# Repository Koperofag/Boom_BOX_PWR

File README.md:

# Boom_BOX_PWR
Circuit for powering audio amplifier using a 3S llithium battery and charging circuit for it.

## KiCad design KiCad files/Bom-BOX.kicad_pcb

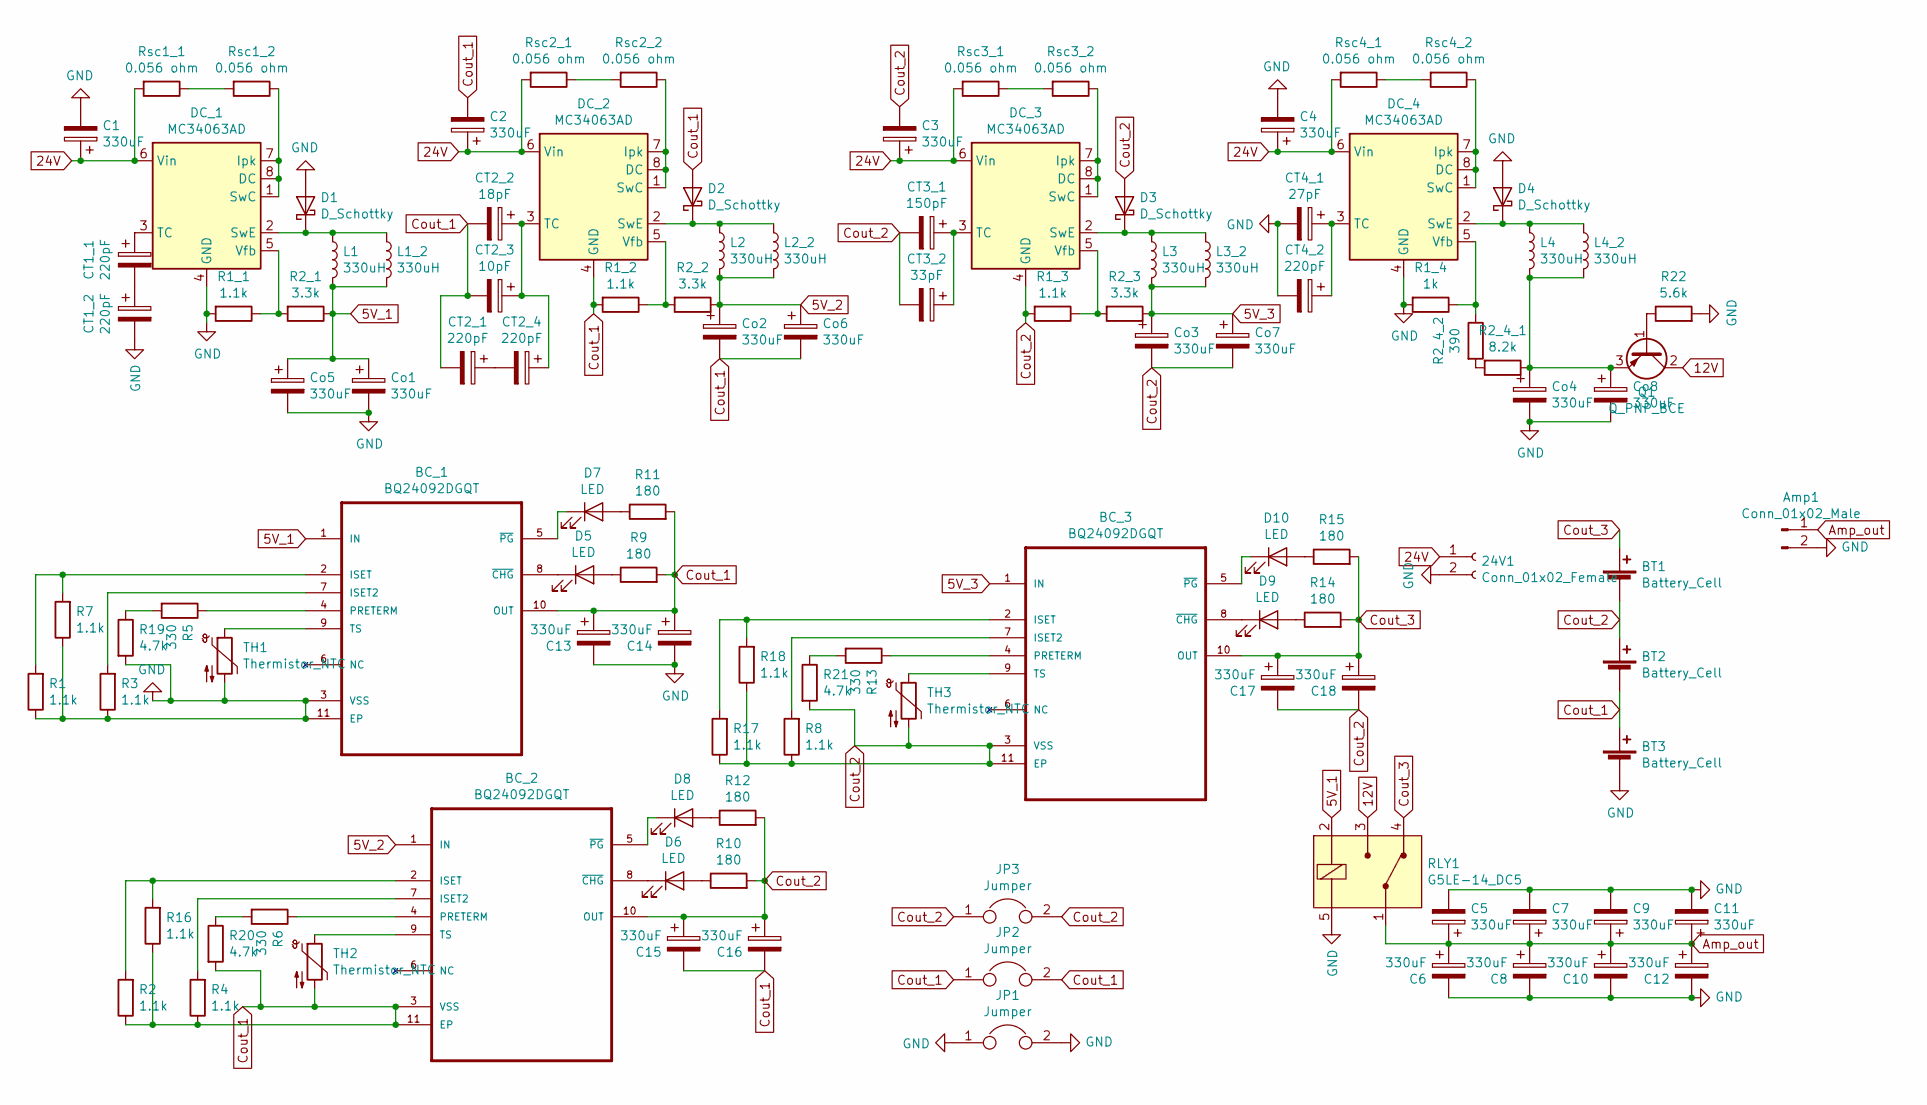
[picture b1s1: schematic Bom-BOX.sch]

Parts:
24V1: Conn_01x02_Female; TerminalBlock_RND_205-00001_1x02_P5.00mm_Horizontal
Amp1: Conn_01x02_Male; TerminalBlock_RND_205-00001_1x02_P5.00mm_Horizontal
BC_1, BC_2, BC_3: BQ24092DGQT; SOP50P490X110-11N
BT1, BT2, BT3: Battery_Cell; TerminalBlock_RND_205-00001_1x02_P5.00mm_Horizontal
C1, C2, C3, C4, C5, C6, C7, C8, C9, C10, C11, C12, C13, C14, C15, C16, C17, C18: 330uF; CP_Radial_D8.0mm_P5.00mm
CT1_1, CT1_2, CT2_1, CT2_4, CT4_2: 220pF; C_0603_1608Metric_Pad1.05x0.95mm_HandSolder
CT2_2: 18pF; C_0603_1608Metric_Pad1.05x0.95mm_HandSolder
CT2_3: 10pF; C_0603_1608Metric_Pad1.05x0.95mm_HandSolder
CT3_1: 150pF; C_0603_1608Metric_Pad1.05x0.95mm_HandSolder
CT3_2: 33pF; C_0603_1608Metric_Pad1.05x0.95mm_HandSolder
CT4_1: 27pF; C_0603_1608Metric_Pad1.05x0.95mm_HandSolder
Co1, Co2, Co3, Co4, Co5, Co6, Co7, Co8: 330uF; CP_Radial_D8.0mm_P5.00mm
D1, D2, D3, D4: D_Schottky; DO-214AB_ALT
D5, D6, D7, D8, D9, D10: LED; LED_D5.0mm
DC_1, DC_2, DC_3, DC_4: MC34063AD; SOIC-8_3.9x4.9mm_P1.27mm
JP1, JP2, JP3: Jumper; SolderWirePad_1x02_P3.81mm_Drill1mm
L1, L1_2, L2, L2_2, L3, L3_2, L4, L4_2: 330uH; L_Bourns_SRR1210A
Q1: Q_PNP_BCE; TO-220-3_Vertical
R1, R1_1, R1_2, R1_3, R2, R3, R4, R7, R8, R16, R17, R18: 1.1k; R_0603_1608Metric_Pad1.05x0.95mm_HandSolder
R1_4: 1k; R_0805_2012Metric_Pad1.15x1.40mm_HandSolder
R2_1, R2_2, R2_3: 3.3k; R_0805_2012Metric_Pad1.15x1.40mm_HandSolder
R2_4_1: 8.2k; R_0805_2012Metric_Pad1.15x1.40mm_HandSolder
R2_4_2: 390; R_0805_2012Metric_Pad1.15x1.40mm_HandSolder
R5, R6, R13: 330; R_0805_2012Metric_Pad1.15x1.40mm_HandSolder
R9, R10, R11, R12, R14, R15: 180; R_0603_1608Metric_Pad1.05x0.95mm_HandSolder
R19, R20, R21: 4.7k; R_0805_2012Metric_Pad1.15x1.40mm_HandSolder
R22: 5.6k; R_Axial_DIN0207_L6.3mm_D2.5mm_P10.16mm_Horizontal
RLY1: G5LE-14_DC5; Relay_THT_G5LE-14; MPN G5LE-14 DC5; Digi-Key_PN Z1011-ND
Rsc1_1, Rsc1_2, Rsc2_1, Rsc2_2, Rsc3_1, Rsc3_2, Rsc4_1, Rsc4_2: 0.056 ohm; C_0805_2012Metric_Pad1.15x1.40mm_HandSolder
TH1, TH2, TH3: Thermistor_NTC; R_Axial_DIN0309_L9.0mm_D3.2mm_P5.08mm_Vertical

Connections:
5V_1: BC_1.1 (IN), Co1.1, Co5.1, L1.2, L1_2.2, R2_1.1, RLY1.2 (COIL)
5V_2: BC_2.1 (IN), Co2.1, Co6.1, L2.2, L2_2.2, R2_2.1
5V_3: BC_3.1 (IN), Co3.1, Co7.1, L3.2, L3_2.2, R2_3.1
12V: Q1.2 (C), RLY1.3 (NO)
24V: 24V1.1, C1.1, C2.1, C3.1, C4.1, DC_1.6 (Vin), DC_2.6 (Vin), DC_3.6 (Vin), DC_4.6 (Vin), Rsc1_1.2, Rsc2_1.2, Rsc3_1.2, Rsc4_1.2
Amp_out: Amp1.1, C5.1, C6.1, C7.1, C8.1, C9.1, C10.1, C11.1, C12.1, RLY1.1 (COM)
Cout_1: BC_1.10 (OUT), BC_2.3 (VSS), BC_2.11 (EP), BT2.2 (-), BT3.1 (+), C2.2, C13.1, C14.1, C15.2, C16.2, CT2_1.2, CT2_2.2, CT2_3.2, Co2.2, Co6.2, D2.2 (A), DC_2.4 (GND), JP2.1, JP2.2, R1_2.2, R2.1, R4.1, R9.2, R11.2, R16.1, R20.2, TH2.2
Cout_2: BC_2.10 (OUT), BC_3.3 (VSS), BC_3.11 (EP), BT1.2 (-), BT2.1 (+), C3.2, C15.1, C16.1, C17.2, C18.2, CT3_1.2, CT3_2.2, Co3.2, Co7.2, D3.2 (A), DC_3.4 (GND), JP3.1, JP3.2, R1_3.2, R8.1, R10.2, R12.2, R17.1, R18.1, R21.2, TH3.2
Cout_3: BC_3.10 (OUT), BT1.1 (+), C17.1, C18.1, R14.2, R15.2, RLY1.4 (NC)
GND: 24V1.2, Amp1.2, BC_1.3 (VSS), BC_1.11 (EP), BT3.2 (-), C1.2, C4.2, C5.2, C6.2, C7.2, C8.2, C9.2, C10.2, C11.2, C12.2, C13.2, C14.2, CT1_2.2, CT4_1.2, CT4_2.2, Co1.2, Co4.2, Co5.2, Co8.2, D1.2 (A), D4.2 (A), DC_1.4 (GND), DC_4.4 (GND), JP1.1, JP1.2, R1.1, R1_1.2, R1_4.2, R3.1, R7.1, R19.2, R22.2, RLY1.5 (COIL), TH1.2
unnamed: BC_1.2 (ISET), R1.2, R7.2
unnamed: BC_1.4 (PRETERM), R5.1
unnamed: BC_1.5 (~PG), D7.1 (K)
unnamed: BC_1.7 (ISET2), R3.2
unnamed: BC_1.8 (~CHG), D5.1 (K)
unnamed: BC_1.9 (TS), TH1.1
unnamed: BC_2.2 (ISET), R2.2, R16.2
unnamed: BC_2.4 (PRETERM), R6.1
unnamed: BC_2.5 (~PG), D8.1 (K)
unnamed: BC_2.7 (ISET2), R4.2
unnamed: BC_2.8 (~CHG), D6.1 (K)
unnamed: BC_2.9 (TS), TH2.1
unnamed: BC_3.2 (ISET), R17.2, R18.2
unnamed: BC_3.4 (PRETERM), R13.1
unnamed: BC_3.5 (~PG), D10.1 (K)
unnamed: BC_3.7 (ISET2), R8.2
unnamed: BC_3.8 (~CHG), D9.1 (K)
unnamed: BC_3.9 (TS), TH3.1
unnamed: CT1_1.1, DC_1.3 (TC)
unnamed: CT1_1.2, CT1_2.1
unnamed: CT2_1.1, CT2_4.2
unnamed: CT2_2.1, CT2_3.1, CT2_4.1, DC_2.3 (TC)
unnamed: CT3_1.1, CT3_2.1, DC_3.3 (TC)
unnamed: CT4_1.1, CT4_2.1, DC_4.3 (TC)
unnamed: Co4.1, Co8.1, L4.2, L4_2.2, Q1.3 (E), R2_4_1.1
unnamed: D1.1 (K), DC_1.2 (SwE), L1.1, L1_2.1
unnamed: D2.1 (K), DC_2.2 (SwE), L2.1, L2_2.1
unnamed: D3.1 (K), DC_3.2 (SwE), L3.1, L3_2.1
unnamed: D4.1 (K), DC_4.2 (SwE), L4.1, L4_2.1
unnamed: D5.2 (A), R9.1
unnamed: D6.2 (A), R10.1
unnamed: D7.2 (A), R11.1
unnamed: D8.2 (A), R12.1
unnamed: D9.2 (A), R14.1
unnamed: D10.2 (A), R15.1
unnamed: DC_1.1 (SwC), DC_1.7 (Ipk), DC_1.8 (DC), Rsc1_2.1
unnamed: DC_1.5 (Vfb), R1_1.1, R2_1.2
unnamed: DC_2.1 (SwC), DC_2.7 (Ipk), DC_2.8 (DC), Rsc2_2.1
unnamed: DC_2.5 (Vfb), R1_2.1, R2_2.2
unnamed: DC_3.1 (SwC), DC_3.7 (Ipk), DC_3.8 (DC), Rsc3_2.1
unnamed: DC_3.5 (Vfb), R1_3.1, R2_3.2
unnamed: DC_4.1 (SwC), DC_4.7 (Ipk), DC_4.8 (DC), Rsc4_2.1
unnamed: DC_4.5 (Vfb), R1_4.1, R2_4_2.1
unnamed: Q1.1 (B), R22.1
unnamed: R2_4_1.2, R2_4_2.2
unnamed: R13.2, R21.1
unnamed: R5.2, R19.1
unnamed: R6.2, R20.1
unnamed: Rsc1_1.1, Rsc1_2.2
unnamed: Rsc2_1.1, Rsc2_2.2
unnamed: Rsc3_1.1, Rsc3_2.2
unnamed: Rsc4_1.1, Rsc4_2.2

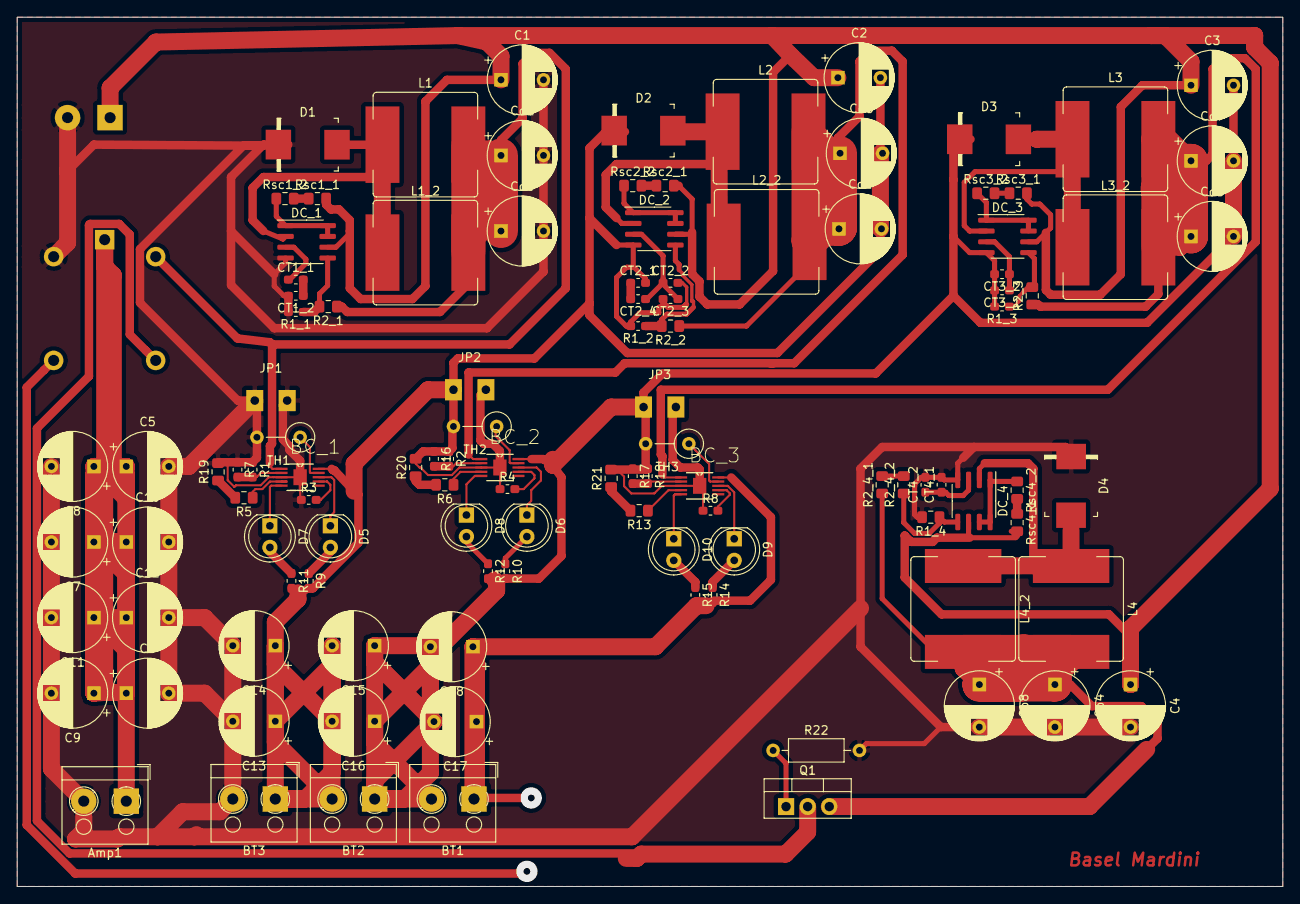
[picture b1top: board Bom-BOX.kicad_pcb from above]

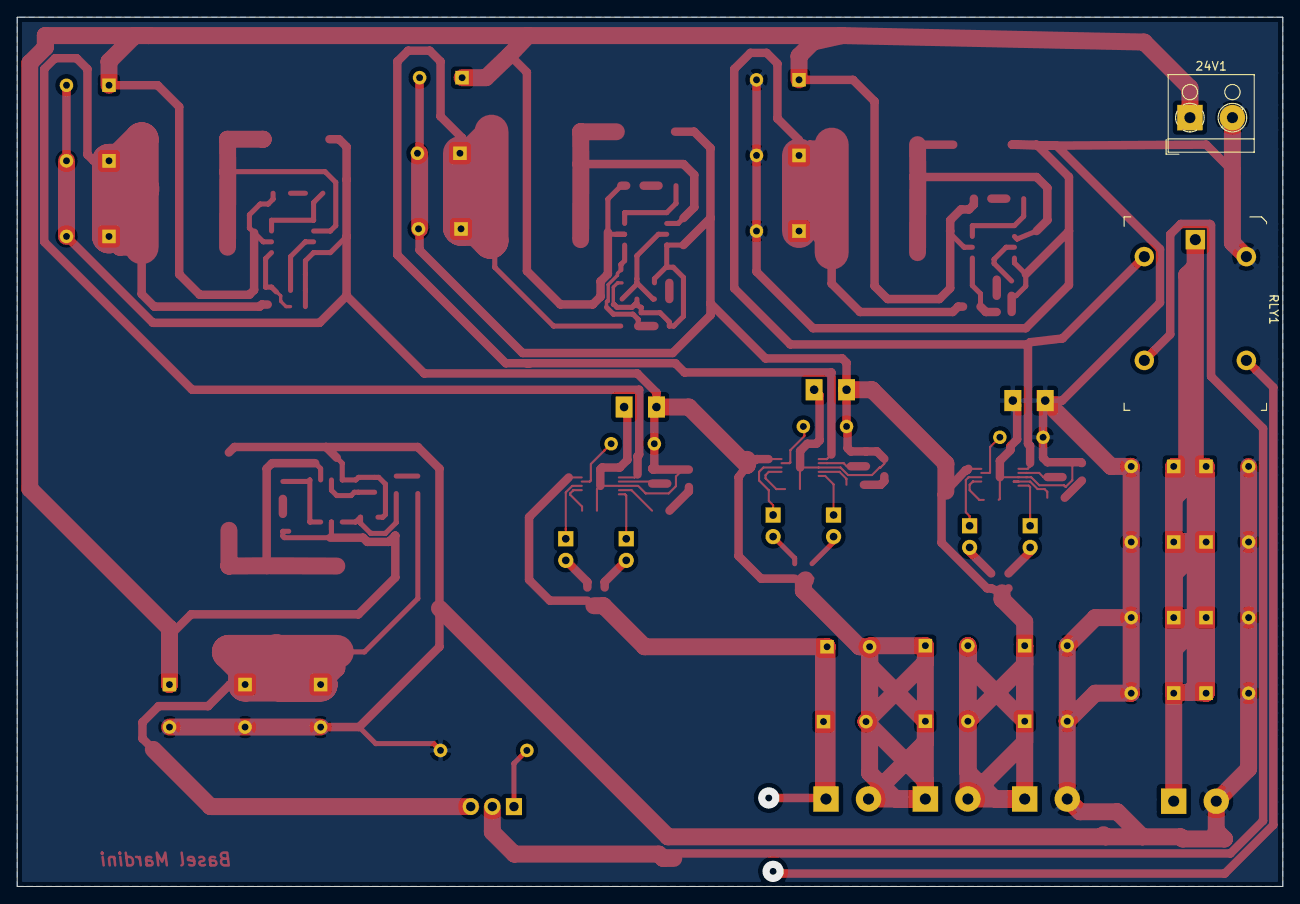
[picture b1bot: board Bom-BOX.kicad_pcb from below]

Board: 2 copper layers, 148.8 x 102.2 mm, 113 parts (2 on the bottom side), 62 nets.

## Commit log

2020-08-19 Current version
    Current work that has been done since the beginning of the project.
